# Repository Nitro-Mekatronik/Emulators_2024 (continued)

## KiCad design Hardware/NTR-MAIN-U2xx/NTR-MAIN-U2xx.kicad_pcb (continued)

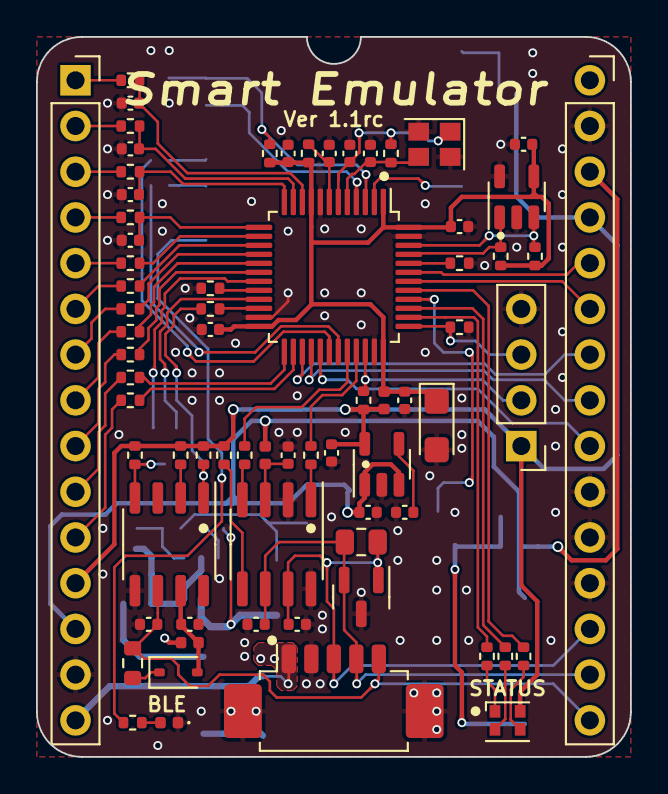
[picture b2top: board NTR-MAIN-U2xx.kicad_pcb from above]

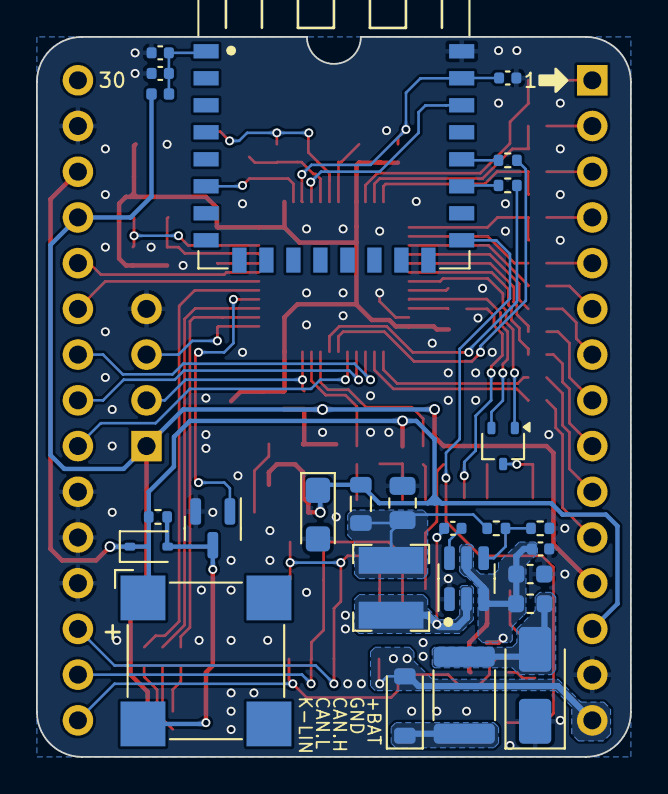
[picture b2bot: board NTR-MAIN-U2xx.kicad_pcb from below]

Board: 2 copper layers, 33.0 x 40.0 mm, 97 parts (26 on the bottom side), 84 nets.

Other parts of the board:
C26: 10uF 10V; CP_EIA-3216-10_Kemet-I
C27, C28, C29, C30: 10nF 50V; C_0402_1005Metric
FB5: 150Ω@100MHz; L_0402_1005Metric

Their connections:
+3.3V: FB5.2; also elsewhere on the board

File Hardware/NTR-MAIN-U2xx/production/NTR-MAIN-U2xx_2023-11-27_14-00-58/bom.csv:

Designator,Footprint,Quantity,Value,LCSC Part #
BZ1,MagneticBuzzer_CUI_CMT-8504-100-SMT,1,Buzzer,C255315
"C1, C10, C11, C13, C15, C16, C17, C22, C23, C24, C25, C4, C5, C8",0402,14,100nF 50V,C77020
C12,0402,1,220pF 50V,C107025
C14,0603,1,4.7uF 35V,C162274
"C18, C27, C28, C29, C30",0402,5,10nF 50V,C15195
"C19, C9",0402,2,10uF 10V,C315248
"C2, C3",0402,2,12pF,C76948
C20,0805,1,22uF 10V,C380336
C21,CP_EIA-3216-10_Kemet-I,1,22uF 16V,C782264
C26,CP_EIA-3216-10_Kemet-I,1,10uF 10V,C7177
"C6, C7",0402,2,47pF 50V,C76970
"D1, D5",D_SOD-323,2,B0530WS,C2961213
D2,LED_Cree-PLCC4_2x2mm_CW,1,RGB,C375569
D3,SOT-23,1,NUP2105LT1G,C2890118
D4,0402,1,LED.O,C434447
D6,D_SMA,1,SMAJ30CA,C356367
D7,D_SOD-123,1,1N4007W,C3018540
F1,1812,1,1A,C782762
"FB1, FB2, FB5, FB6",0402,4,150Ω@100MHz,C160612
FB3,0603,1,300Ω@100MHz,C401489
FB4,0805,1,300Ω@100MHz,C67451
"J1, J2",PinSocket_1x15_P2.54mm_Vertical,2,Conn_01x15,C2897378
J3,Molex_PicoBlade_53261-0571_1x05-1MP_P1.25mm_Horizontal,1,Conn_01x05,C481427
J4,PinHeader_1x04_P2.54mm_Vertical,1,SW,
L1,L_Bourns-SRN4018,1,10uH,C135244
Q1,SOT-23,1,2N7002K,C2848187
"R1, R16, R2, R4",0402,4,10KΩ,C25744
"R10, R9",0402,2,4.7KΩ,C25900
"R11, R12, R13, R17, R18, R25, R26, R27, R28, R29, R30, R31, R32, R33, R34, R35, R36, R37",0402,18,100Ω,C25076
R14,0805,1,120Ω,C17437
"R15, R5",0402,2,150Ω,C25082
R20,0603,1,1K,C21190
"R21, R23, R24",0402,3,100KΩ,C25741
R22,0402,1,13.7KΩ,C25854
R3,0402,1,1MΩ,C138033
"R6, R7",0402,2,47Ω,C25168
R8,0402,1,1KΩ,C11702
U1,LQFP-48_7x7mm_P0.5mm,1,STM32F103CBT6,C8304
U2,SOT-23-5,1,FT24C64A,C5263778
U3,SOIC-8_3.9x4.9mm_P1.27mm,1,TJA1051T/3,C5342108
U4,JDY-08,1,YM23,C2905738
U5,SOT-353_SC-70-5,1,74AHC1G08SE-7,C459531
U6,SO-8_3.9x4.9mm_P1.27mm,1,TJA1027T,C194371
U7,SOT-23-6,1,LMR51420XDDCR,C5246146
U8,SOT-23-5,1,LP2985A-33DBVR,C89826
Y1,Crystal_SMD_2520-4Pin_2.5x2.0mm,1,16MHZ,C13738

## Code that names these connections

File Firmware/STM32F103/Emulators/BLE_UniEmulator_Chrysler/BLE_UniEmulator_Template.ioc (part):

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Mcu.Name=STM32F103C(8-B)Tx
Mcu.Package=LQFP48
Mcu.UserName=STM32F103CBTx
PA0-WKUP.Signal=ADCx_IN0
PA1.Signal=ADCx_IN1
PA10.Mode=Asynchronous
PA10.Signal=USART1_RX
PA11.Mode=CAN_Activate
PA11.Signal=CAN_RX
PA12.Mode=CAN_Activate
PA12.Signal=CAN_TX
PA13.Mode=Serial_Wire
PA13.Signal=SYS_JTMS-SWDIO
PA14.Mode=Serial_Wire
PA14.Signal=SYS_JTCK-SWCLK
PA15.GPIOParameters=GPIO_Label
PA15.GPIO_Label=LED_B
PA15.Signal=GPIO_Output
PA2.Signal=ADCx_IN2
PA3.Signal=ADCx_IN3
PA4.Mode=NSS_Signal_Hard_Output
PA4.Signal=SPI1_NSS
PA5.Mode=Full_Duplex_Master
PA5.Signal=SPI1_SCK
PA6.Mode=Full_Duplex_Master
PA6.Signal=SPI1_MISO
PA7.Mode=Full_Duplex_Master
PA7.Signal=SPI1_MOSI
PA8.Mode=Clock-out
PA8.Signal=RCC_MCO
PA9.Mode=Asynchronous
PA9.Signal=USART1_TX
PB0.Signal=GPXTI0
PB1.GPIOParameters=GPIO_Label
PB1.GPIO_Label=KLINE_MODE
PB1.Signal=GPIO_Output
PB10.Mode=LIN
PB10.Signal=USART3_TX
PB11.Mode=LIN
PB11.Signal=USART3_RX
PB12.GPIOParameters=GPIO_Label
PB12.GPIO_Label=DI1
PB12.Signal=GPIO_Input
PB13.GPIOParameters=GPIO_Label
PB13.GPIO_Label=DI2
PB13.Signal=GPIO_Input
PB14.GPIOParameters=GPIO_Label
PB14.GPIO_Label=DO1
PB14.Signal=GPIO_Output
PB15.GPIOParameters=GPIO_Label
PB15.GPIO_Label=DO2
PB15.Signal=GPIO_Output
PB3.GPIOParameters=GPIO_Label
PB3.GPIO_Label=LED_G
PB3.Signal=GPIO_Output
PB4.Signal=S_TIM3_CH1
PB5.GPIOParameters=GPIO_Label
PB5.GPIO_Label=LED_R
PB5.Signal=GPIO_Output
PB6.Signal=S_TIM4_CH1
PB7.Signal=S_TIM4_CH2
PB8.Mode=I2C
PB8.Signal=I2C1_SCL
PB9.Mode=I2C
PB9.Signal=I2C1_SDA
PC13-TAMPER-RTC.GPIOParameters=GPIO_Label
PC13-TAMPER-RTC.GPIO_Label=BLE_STATUS
PC13-TAMPER-RTC.Signal=GPIO_Input
PC14-OSC32_IN.GPIOParameters=GPIO_Label
PC14-OSC32_IN.GPIO_Label=BLE_nRST
PC14-OSC32_IN.Signal=GPIO_Output
PC15-OSC32_OUT.GPIOParameters=GPIO_Label
PC15-OSC32_OUT.GPIO_Label=BLE_AT_MODE
PC15-OSC32_OUT.Signal=GPIO_Output
PD0-OSC_IN.Mode=HSE-External-Oscillator
PD0-OSC_IN.Signal=RCC_OSC_IN
PD1-OSC_OUT.Mode=HSE-External-Oscillator
PD1-OSC_OUT.Signal=RCC_OSC_OUT
RCC.HSEDivPLL=RCC_HSE_PREDIV_DIV2
RCC.HSE_VALUE=16000000
RCC.SYSCLKFreq_VALUE=72000000
RCC.SYSCLKSource=RCC_SYSCLKSOURCE_PLLCLK
board=custom

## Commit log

2024-02-26 add HW FW and Boot
2024-03-15 update SerialFIFO & Device Info
2024-03-15 add shield number in device info res
2024-04-15 add V40 and arduino HW
2024-05-07 add new SerialProtocol V1.5.1 and SmartLED Update
2024-08-20 update bootloader
2024-08-20 Activate bootloader if EEPROM is empty
2024-09-03 BMW Parity Bug
2024-09-24 update boot and app
2024-09-25 fix bug Boot BLE Disable
2024-09-25 fifo change buffer size to 128 bytes and timeout 100ms
2024-09-25 update boot serial fifo with timeout 100ms
2024-09-25 fix bug in startup BLE Reset
2025-08-07 Initial commit: Project setup with documentation and basic structure
